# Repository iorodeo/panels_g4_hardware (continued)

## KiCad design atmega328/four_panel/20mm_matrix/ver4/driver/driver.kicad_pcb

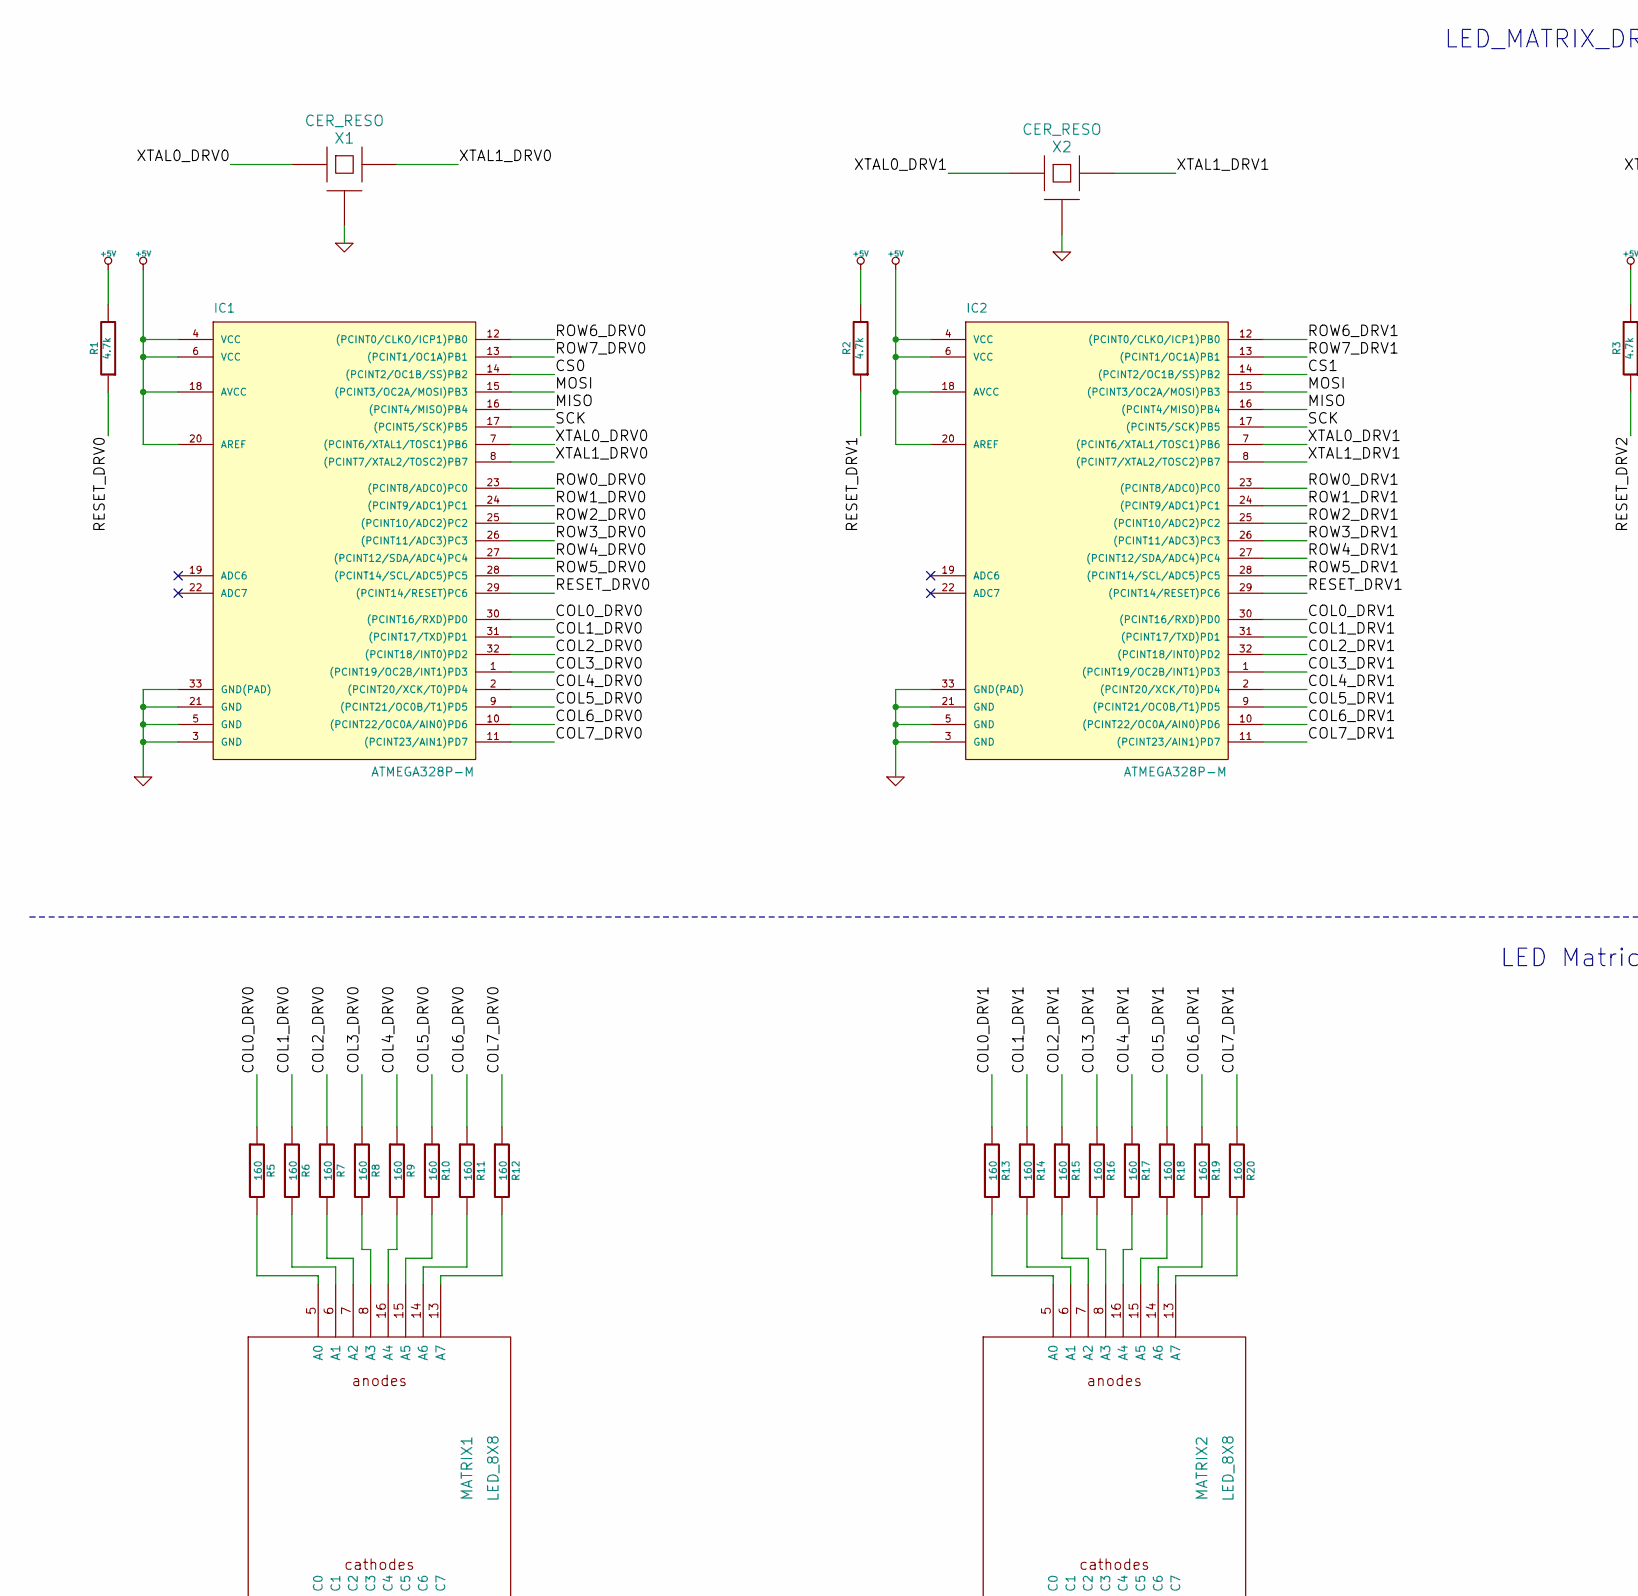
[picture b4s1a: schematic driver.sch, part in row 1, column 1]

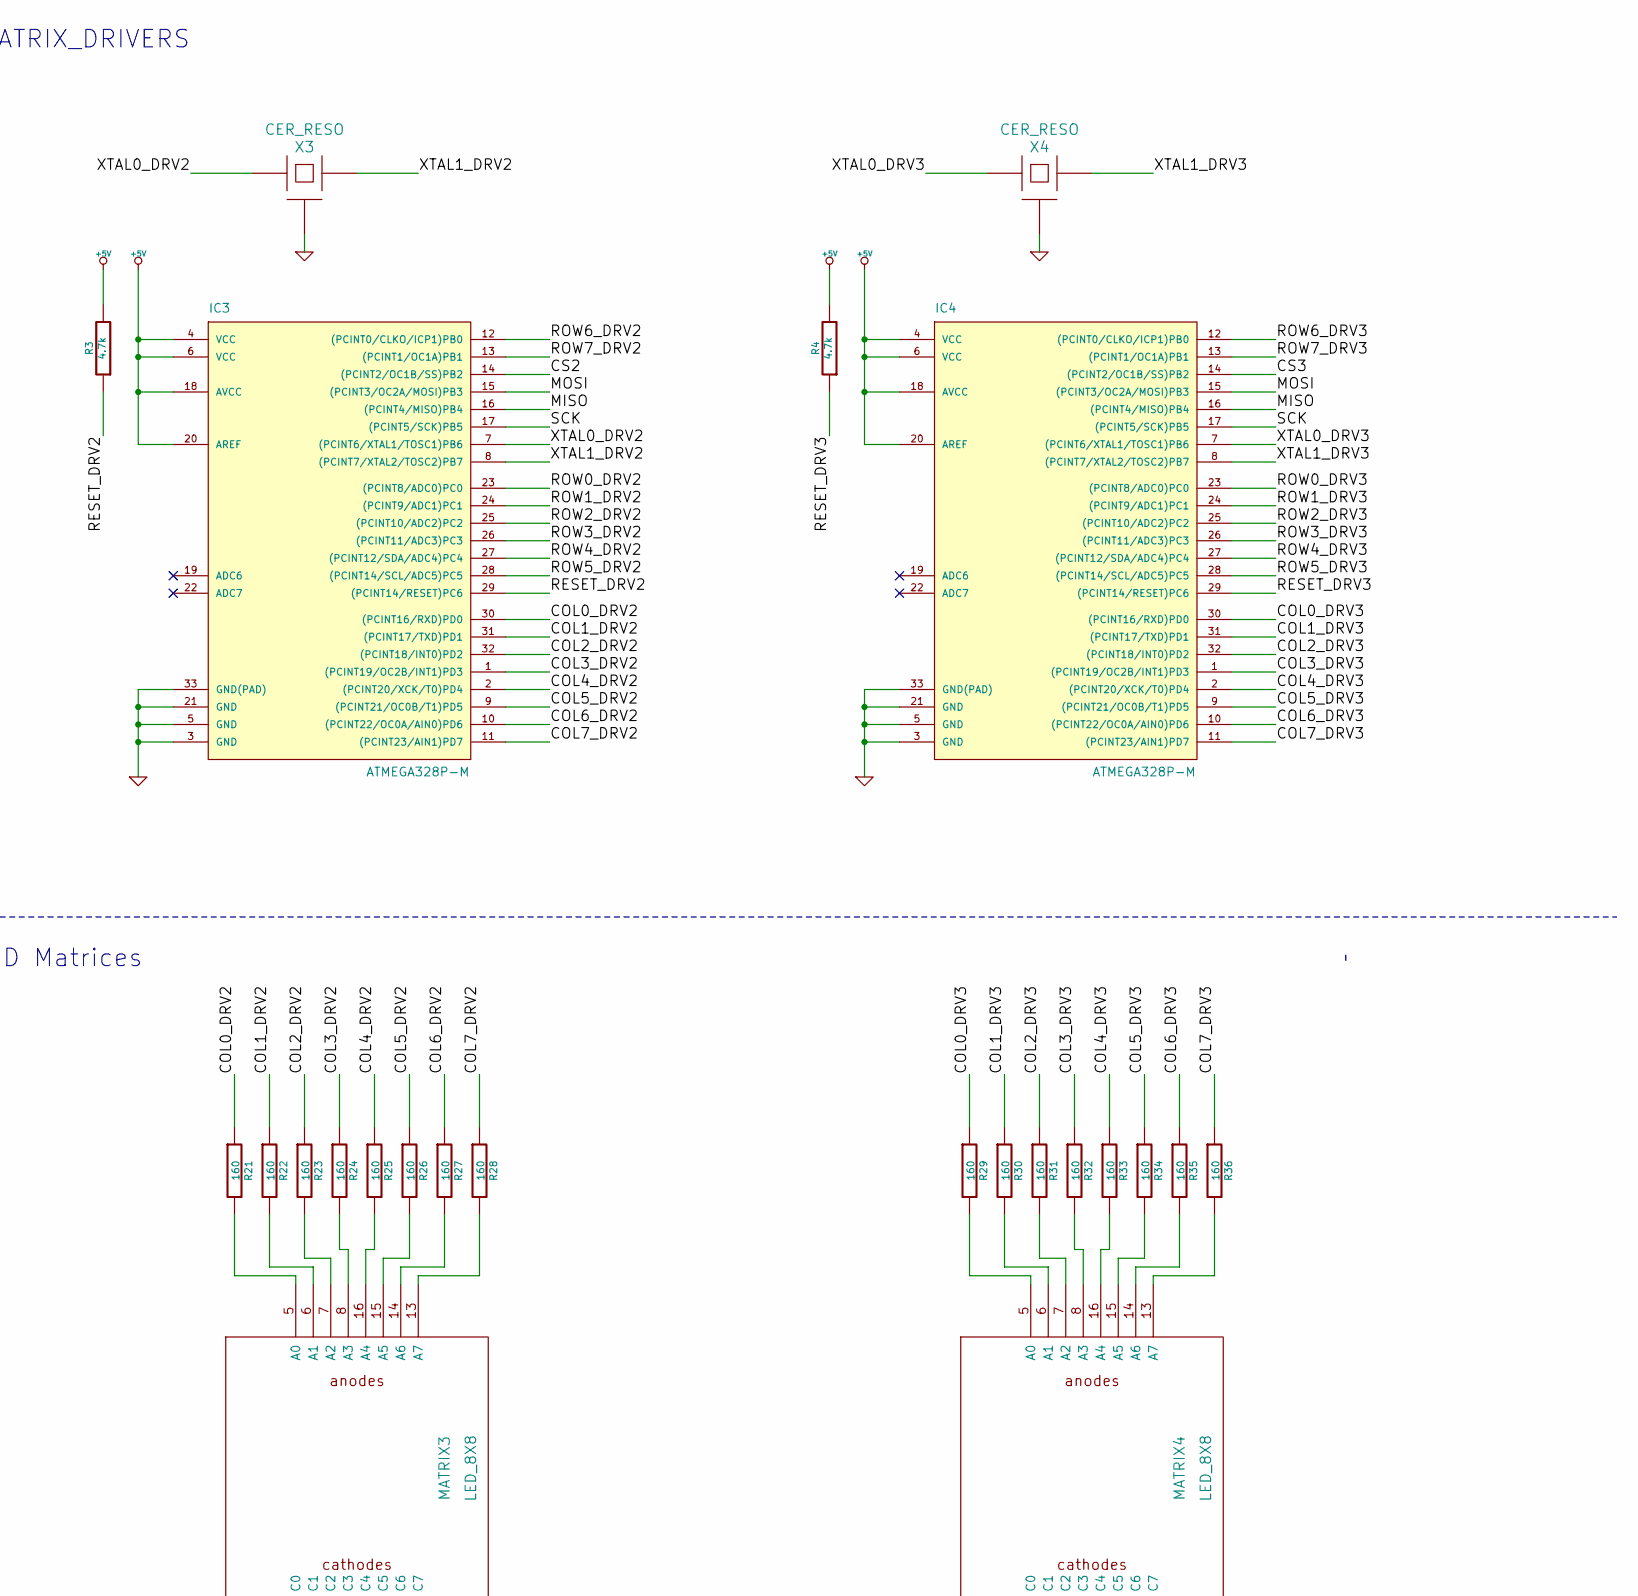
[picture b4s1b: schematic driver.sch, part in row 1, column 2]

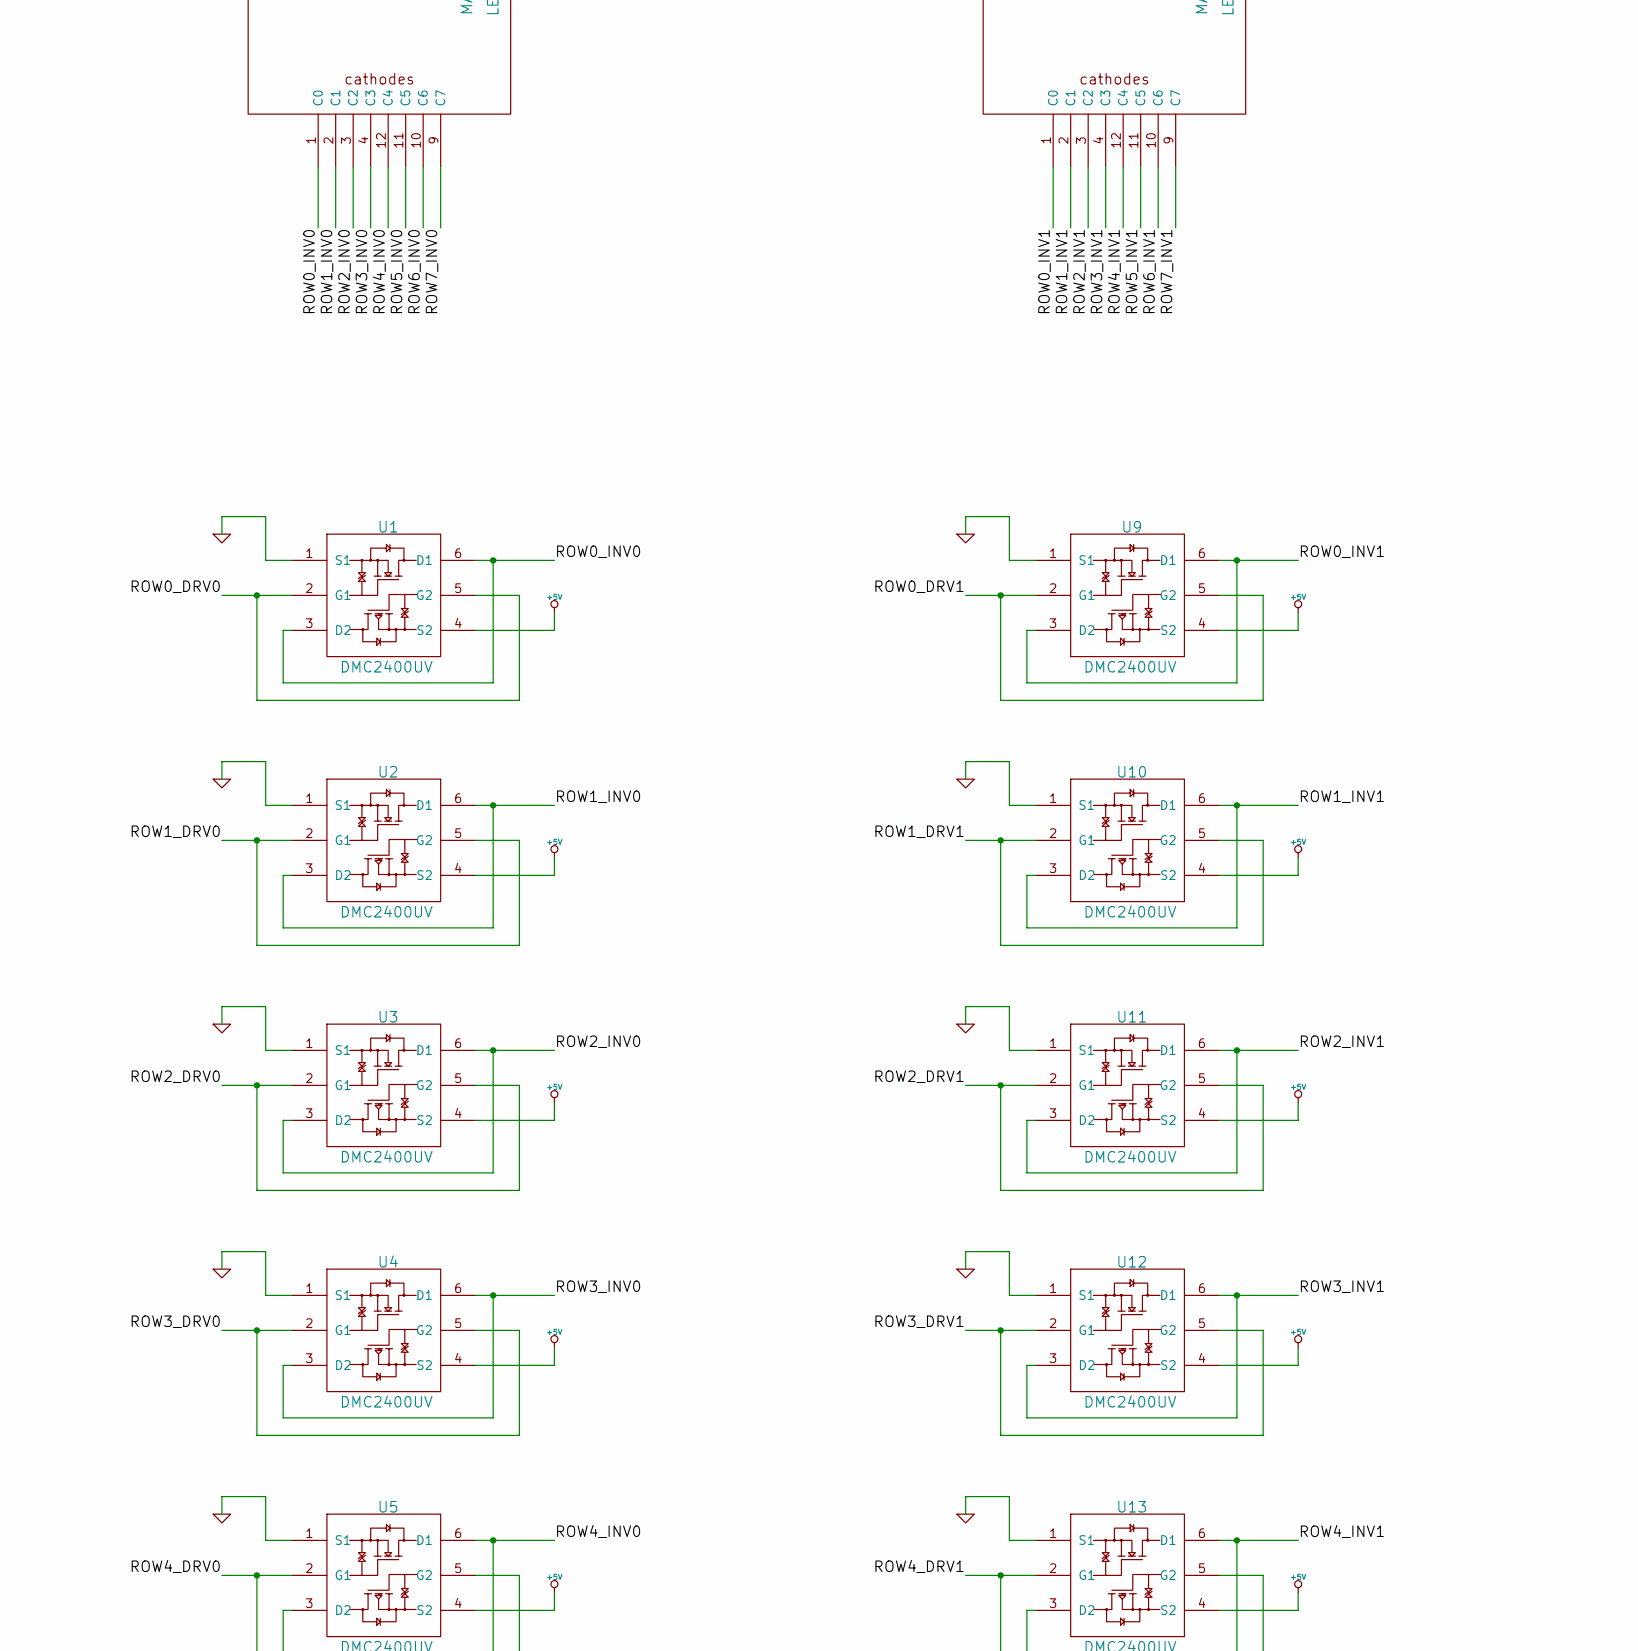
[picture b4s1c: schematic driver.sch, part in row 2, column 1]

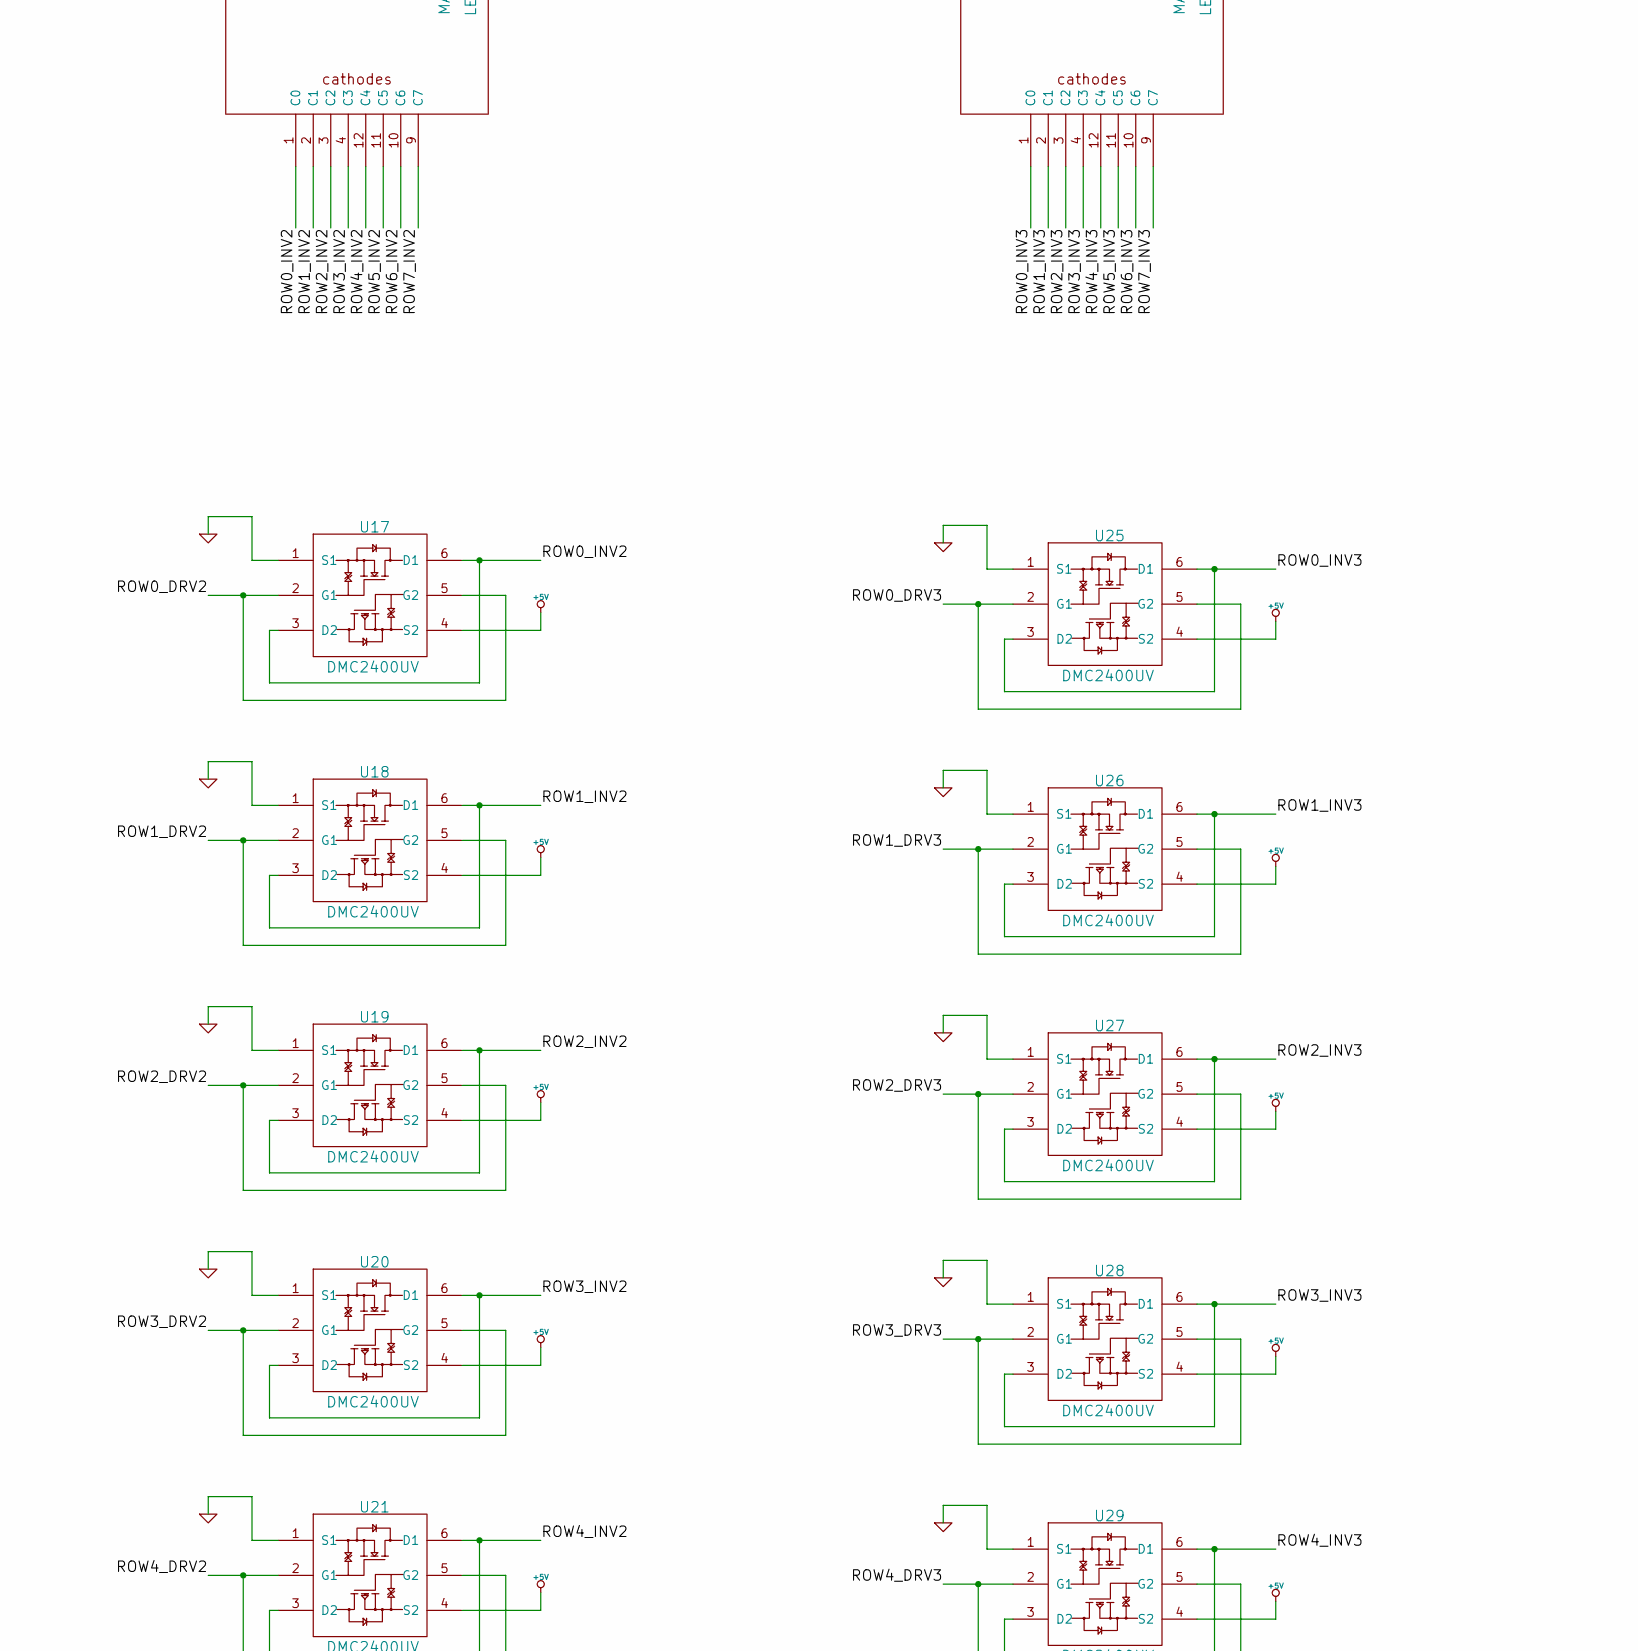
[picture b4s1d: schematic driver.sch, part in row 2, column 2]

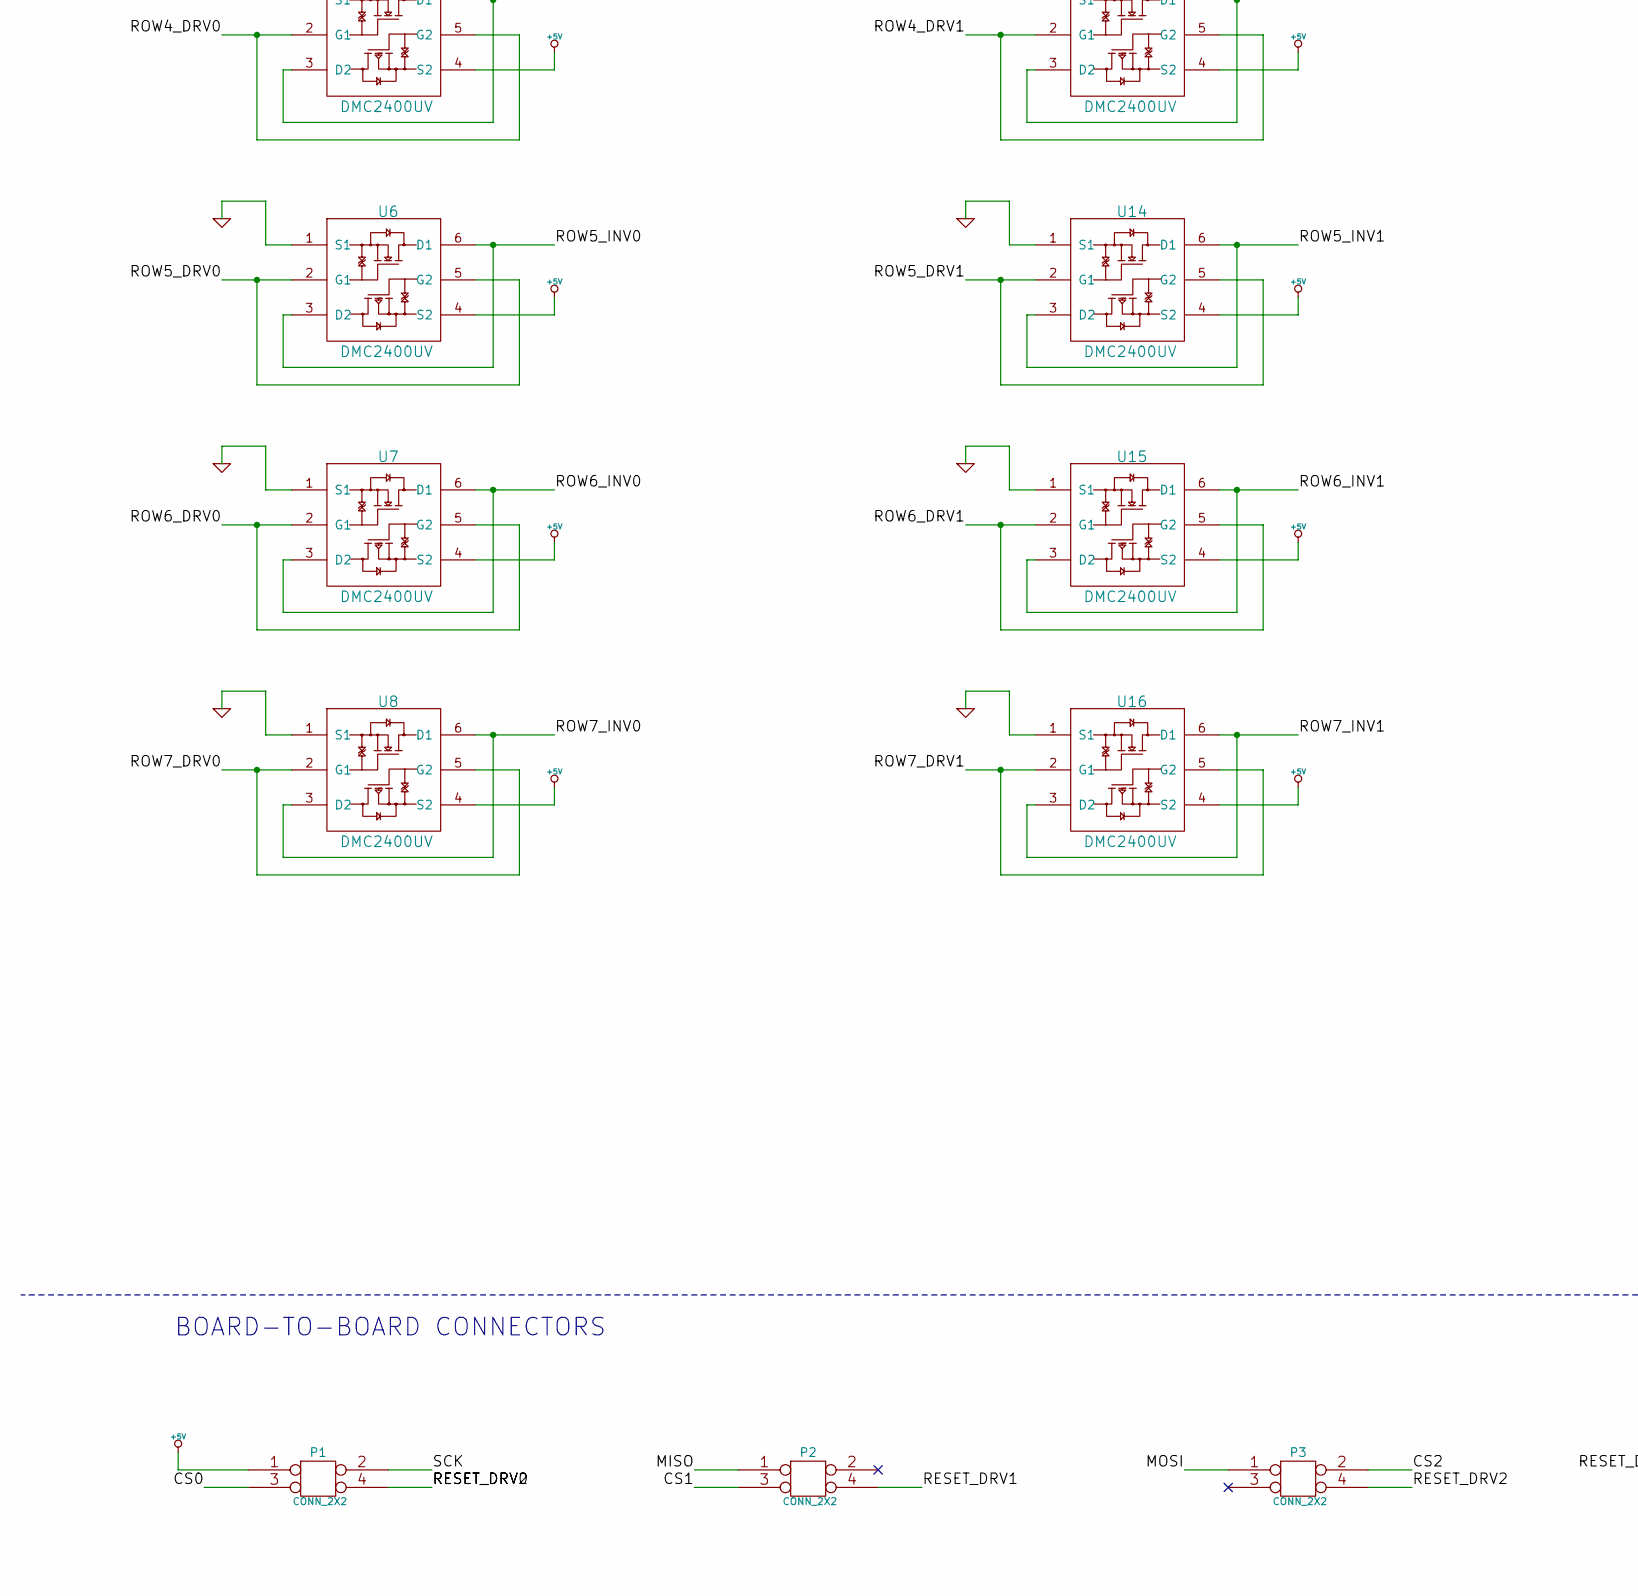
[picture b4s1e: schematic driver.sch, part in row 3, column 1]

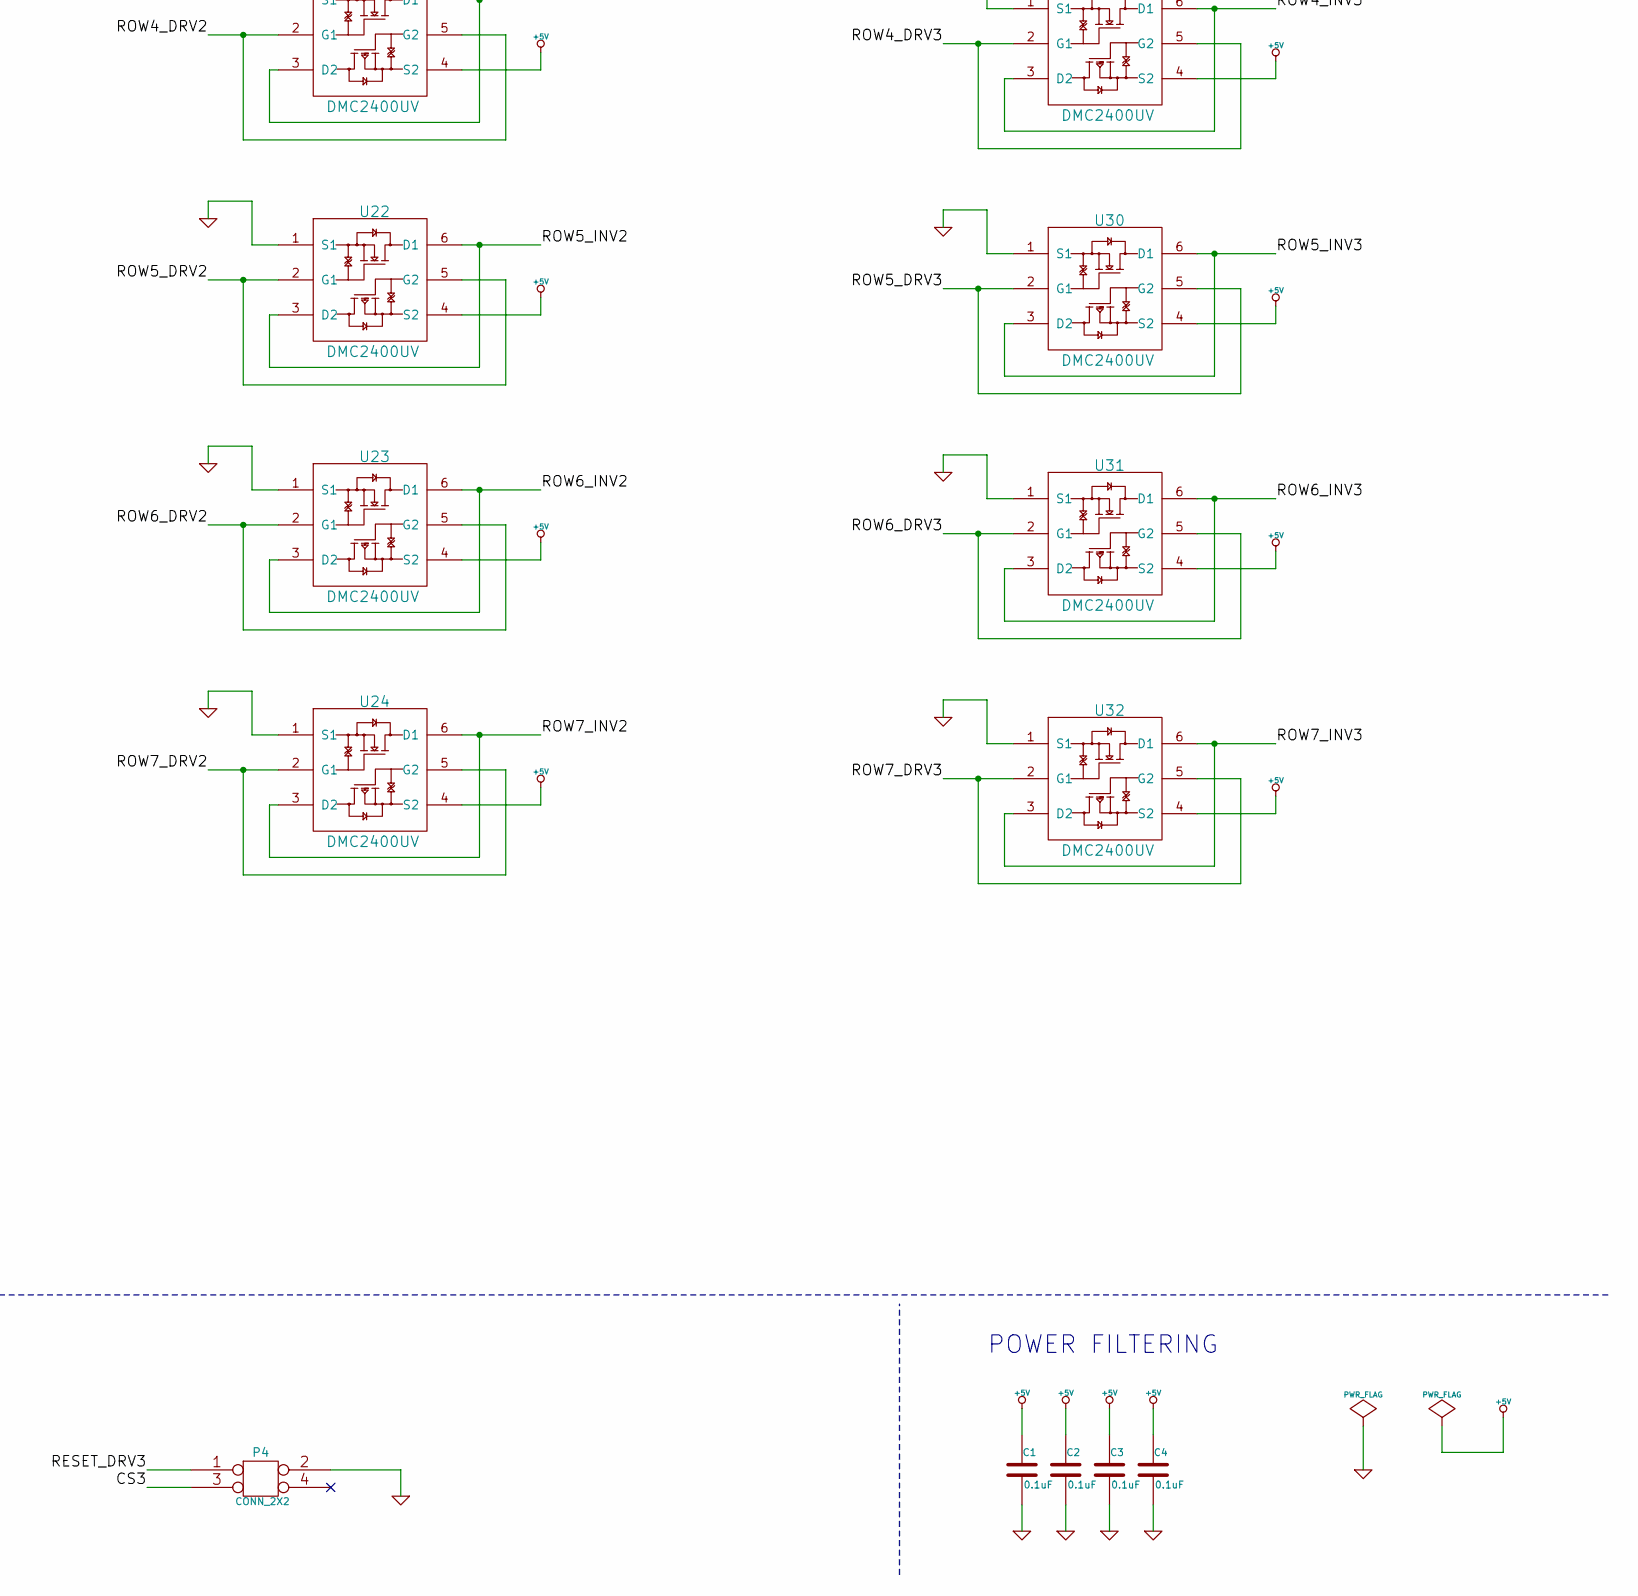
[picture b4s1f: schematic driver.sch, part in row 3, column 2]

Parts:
C1, C2, C3, C4: 0.1uF
IC1, IC2, IC3, IC4: ATMEGA328P-M; MLF/QFN32
MATRIX1, MATRIX2, MATRIX3, MATRIX4: LED_8X8
P1, P2, P3, P4: CONN_2X2
R1, R2, R3, R4: 4.7k
R5, R6, R7, R8, R9, R10, R11, R12, R13, R14, R15, R16, R17, R18, R19, R20, R21, R22, R23, R24, R25, R26, R27, R28, R29, R30, R31, R32, R33, R34, R35, R36: 160
U1, U2, U3, U4, U5, U6, U7, U8, U9, U10, U11, U12, U13, U14, U15, U16, U17, U18, U19, U20, U21, U22, U23, U24, U25, U26, U27, U28, U29, U30, U31, U32: DMC2400UV
X1, X2, X3, X4: CER_RESO

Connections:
+5V: C1.1, C2.1, C3.1, C4.1, IC1.4 (VCC), IC1.6 (VCC), IC1.18 (AVCC), IC1.20 (AREF), IC2.4 (VCC), IC2.6 (VCC), IC2.18 (AVCC), IC2.20 (AREF), IC3.4 (VCC), IC3.6 (VCC), IC3.18 (AVCC), IC3.20 (AREF), IC4.4 (VCC), IC4.6 (VCC), IC4.18 (AVCC), IC4.20 (AREF), P1.1, R1.2, R2.2, R3.2, R4.2, U1.4 (S2), U2.4 (S2), U3.4 (S2), U4.4 (S2), U5.4 (S2), U6.4 (S2), U7.4 (S2), U8.4 (S2), U9.4 (S2), U10.4 (S2), U11.4 (S2), U12.4 (S2), U13.4 (S2), U14.4 (S2), U15.4 (S2), U16.4 (S2), U17.4 (S2), U18.4 (S2), U19.4 (S2), U20.4 (S2), U21.4 (S2), U22.4 (S2), U23.4 (S2), U24.4 (S2), U25.4 (S2), U26.4 (S2), U27.4 (S2), U28.4 (S2), U29.4 (S2), U30.4 (S2), U31.4 (S2), U32.4 (S2)
/COL0_DRV0: IC1.30 ((PCINT16/RXD)PD0), R5.1
/COL0_DRV1: IC2.30 ((PCINT16/RXD)PD0), R13.1
/COL0_DRV2: IC3.30 ((PCINT16/RXD)PD0), R21.1
/COL0_DRV3: IC4.30 ((PCINT16/RXD)PD0), R29.1
/COL1_DRV0: IC1.31 ((PCINT17/TXD)PD1), R6.1
/COL1_DRV1: IC2.31 ((PCINT17/TXD)PD1), R14.1
/COL1_DRV2: IC3.31 ((PCINT17/TXD)PD1), R22.1
/COL1_DRV3: IC4.31 ((PCINT17/TXD)PD1), R30.1
/COL2_DRV0: IC1.32 ((PCINT18/INT0)PD2), R7.1
/COL2_DRV1: IC2.32 ((PCINT18/INT0)PD2), R15.1
/COL2_DRV2: IC3.32 ((PCINT18/INT0)PD2), R23.1
/COL2_DRV3: IC4.32 ((PCINT18/INT0)PD2), R31.1
/COL3_DRV0: IC1.1 ((PCINT19/OC2B/INT1)PD3), R8.1
/COL3_DRV1: IC2.1 ((PCINT19/OC2B/INT1)PD3), R16.1
/COL3_DRV2: IC3.1 ((PCINT19/OC2B/INT1)PD3), R24.1
/COL3_DRV3: IC4.1 ((PCINT19/OC2B/INT1)PD3), R32.1
/COL4_DRV0: IC1.2 ((PCINT20/XCK/T0)PD4), R9.1
/COL4_DRV1: IC2.2 ((PCINT20/XCK/T0)PD4), R17.1
/COL4_DRV2: IC3.2 ((PCINT20/XCK/T0)PD4), R25.1
/COL4_DRV3: IC4.2 ((PCINT20/XCK/T0)PD4), R33.1
/COL5_DRV0: IC1.9 ((PCINT21/OC0B/T1)PD5), R10.1
/COL5_DRV1: IC2.9 ((PCINT21/OC0B/T1)PD5), R18.1
/COL5_DRV2: IC3.9 ((PCINT21/OC0B/T1)PD5), R26.1
/COL5_DRV3: IC4.9 ((PCINT21/OC0B/T1)PD5), R34.1
/COL6_DRV0: IC1.10 ((PCINT22/OC0A/AIN0)PD6), R11.1
/COL6_DRV1: IC2.10 ((PCINT22/OC0A/AIN0)PD6), R19.1
/COL6_DRV2: IC3.10 ((PCINT22/OC0A/AIN0)PD6), R27.1
/COL6_DRV3: IC4.10 ((PCINT22/OC0A/AIN0)PD6), R35.1
/COL7_DRV0: IC1.11 ((PCINT23/AIN1)PD7), R12.1
/COL7_DRV1: IC2.11 ((PCINT23/AIN1)PD7), R20.1
/COL7_DRV2: IC3.11 ((PCINT23/AIN1)PD7), R28.1
/COL7_DRV3: IC4.11 ((PCINT23/AIN1)PD7), R36.1
/CS0: IC1.14 ((PCINT2/OC1B/SS)PB2), P1.3
/CS1: IC2.14 ((PCINT2/OC1B/SS)PB2), P2.3
/CS2: IC3.14 ((PCINT2/OC1B/SS)PB2), P3.2
/CS3: IC4.14 ((PCINT2/OC1B/SS)PB2), P4.3
/MISO: IC1.16 ((PCINT4/MISO)PB4), IC2.16 ((PCINT4/MISO)PB4), IC3.16 ((PCINT4/MISO)PB4), IC4.16 ((PCINT4/MISO)PB4), P2.1
/MOSI: IC1.15 ((PCINT3/OC2A/MOSI)PB3), IC2.15 ((PCINT3/OC2A/MOSI)PB3), IC3.15 ((PCINT3/OC2A/MOSI)PB3), IC4.15 ((PCINT3/OC2A/MOSI)PB3), P3.1
/RESET_DRV0: IC1.29 ((PCINT14/RESET)PC6), IC3.29 ((PCINT14/RESET)PC6), P1.4, P3.4, R1.1, R3.1
/RESET_DRV1: IC2.29 ((PCINT14/RESET)PC6), P2.4, R2.1
/RESET_DRV3: IC4.29 ((PCINT14/RESET)PC6), P4.1, R4.1
/ROW0_DRV0: IC1.23 ((PCINT8/ADC0)PC0), U1.2 (G1), U1.5 (G2)
/ROW0_DRV1: IC2.23 ((PCINT8/ADC0)PC0), U9.2 (G1), U9.5 (G2)
/ROW0_DRV2: IC3.23 ((PCINT8/ADC0)PC0), U17.2 (G1), U17.5 (G2)
/ROW0_DRV3: IC4.23 ((PCINT8/ADC0)PC0), U25.2 (G1), U25.5 (G2)
/ROW0_INV0: MATRIX1.1 (C0), U1.3 (D2), U1.6 (D1)
/ROW0_INV1: MATRIX2.1 (C0), U9.3 (D2), U9.6 (D1)
/ROW0_INV2: MATRIX3.1 (C0), U17.3 (D2), U17.6 (D1)
/ROW0_INV3: MATRIX4.1 (C0), U25.3 (D2), U25.6 (D1)
/ROW1_DRV0: IC1.24 ((PCINT9/ADC1)PC1), U2.2 (G1), U2.5 (G2)
/ROW1_DRV1: IC2.24 ((PCINT9/ADC1)PC1), U10.2 (G1), U10.5 (G2)
/ROW1_DRV2: IC3.24 ((PCINT9/ADC1)PC1), U18.2 (G1), U18.5 (G2)
/ROW1_DRV3: IC4.24 ((PCINT9/ADC1)PC1), U26.2 (G1), U26.5 (G2)
/ROW1_INV0: MATRIX1.2 (C1), U2.3 (D2), U2.6 (D1)
/ROW1_INV1: MATRIX2.2 (C1), U10.3 (D2), U10.6 (D1)
/ROW1_INV2: MATRIX3.2 (C1), U18.3 (D2), U18.6 (D1)
/ROW1_INV3: MATRIX4.2 (C1), U26.3 (D2), U26.6 (D1)
/ROW2_DRV0: IC1.25 ((PCINT10/ADC2)PC2), U3.2 (G1), U3.5 (G2)
/ROW2_DRV1: IC2.25 ((PCINT10/ADC2)PC2), U11.2 (G1), U11.5 (G2)
/ROW2_DRV2: IC3.25 ((PCINT10/ADC2)PC2), U19.2 (G1), U19.5 (G2)
/ROW2_DRV3: IC4.25 ((PCINT10/ADC2)PC2), U27.2 (G1), U27.5 (G2)
/ROW2_INV0: MATRIX1.3 (C2), U3.3 (D2), U3.6 (D1)
/ROW2_INV1: MATRIX2.3 (C2), U11.3 (D2), U11.6 (D1)
/ROW2_INV2: MATRIX3.3 (C2), U19.3 (D2), U19.6 (D1)
/ROW2_INV3: MATRIX4.3 (C2), U27.3 (D2), U27.6 (D1)
/ROW3_DRV0: IC1.26 ((PCINT11/ADC3)PC3), U4.2 (G1), U4.5 (G2)
/ROW3_DRV1: IC2.26 ((PCINT11/ADC3)PC3), U12.2 (G1), U12.5 (G2)
/ROW3_DRV2: IC3.26 ((PCINT11/ADC3)PC3), U20.2 (G1), U20.5 (G2)
/ROW3_DRV3: IC4.26 ((PCINT11/ADC3)PC3), U28.2 (G1), U28.5 (G2)
/ROW3_INV0: MATRIX1.4 (C3), U4.3 (D2), U4.6 (D1)
/ROW3_INV1: MATRIX2.4 (C3), U12.3 (D2), U12.6 (D1)
/ROW3_INV2: MATRIX3.4 (C3), U20.3 (D2), U20.6 (D1)
/ROW3_INV3: MATRIX4.4 (C3), U28.3 (D2), U28.6 (D1)
/ROW4_DRV0: IC1.27 ((PCINT12/SDA/ADC4)PC4), U5.2 (G1), U5.5 (G2)
/ROW4_DRV1: IC2.27 ((PCINT12/SDA/ADC4)PC4), U13.2 (G1), U13.5 (G2)
/ROW4_DRV2: IC3.27 ((PCINT12/SDA/ADC4)PC4), U21.2 (G1), U21.5 (G2)
/ROW4_DRV3: IC4.27 ((PCINT12/SDA/ADC4)PC4), U29.2 (G1), U29.5 (G2)
/ROW4_INV0: MATRIX1.12 (C4), U5.3 (D2), U5.6 (D1)
/ROW4_INV1: MATRIX2.12 (C4), U13.3 (D2), U13.6 (D1)
/ROW4_INV2: MATRIX3.12 (C4), U21.3 (D2), U21.6 (D1)
/ROW4_INV3: MATRIX4.12 (C4), U29.3 (D2), U29.6 (D1)
/ROW5_DRV0: IC1.28 ((PCINT14/SCL/ADC5)PC5), U6.2 (G1), U6.5 (G2)
/ROW5_DRV1: IC2.28 ((PCINT14/SCL/ADC5)PC5), U14.2 (G1), U14.5 (G2)
/ROW5_DRV2: IC3.28 ((PCINT14/SCL/ADC5)PC5), U22.2 (G1), U22.5 (G2)
/ROW5_DRV3: IC4.28 ((PCINT14/SCL/ADC5)PC5), U30.2 (G1), U30.5 (G2)
/ROW5_INV0: MATRIX1.11 (C5), U6.3 (D2), U6.6 (D1)
/ROW5_INV1: MATRIX2.11 (C5), U14.3 (D2), U14.6 (D1)
/ROW5_INV2: MATRIX3.11 (C5), U22.3 (D2), U22.6 (D1)
/ROW5_INV3: MATRIX4.11 (C5), U30.3 (D2), U30.6 (D1)
/ROW6_DRV0: IC1.12 ((PCINT0/CLKO/ICP1)PB0), U7.2 (G1), U7.5 (G2)
/ROW6_DRV1: IC2.12 ((PCINT0/CLKO/ICP1)PB0), U15.2 (G1), U15.5 (G2)
/ROW6_DRV2: IC3.12 ((PCINT0/CLKO/ICP1)PB0), U23.2 (G1), U23.5 (G2)
/ROW6_DRV3: IC4.12 ((PCINT0/CLKO/ICP1)PB0), U31.2 (G1), U31.5 (G2)
/ROW6_INV0: MATRIX1.10 (C6), U7.3 (D2), U7.6 (D1)
/ROW6_INV1: MATRIX2.10 (C6), U15.3 (D2), U15.6 (D1)
/ROW6_INV2: MATRIX3.10 (C6), U23.3 (D2), U23.6 (D1)
/ROW6_INV3: MATRIX4.10 (C6), U31.3 (D2), U31.6 (D1)
/ROW7_DRV0: IC1.13 ((PCINT1/OC1A)PB1), U8.2 (G1), U8.5 (G2)
/ROW7_DRV1: IC2.13 ((PCINT1/OC1A)PB1), U16.2 (G1), U16.5 (G2)
/ROW7_DRV2: IC3.13 ((PCINT1/OC1A)PB1), U24.2 (G1), U24.5 (G2)
/ROW7_DRV3: IC4.13 ((PCINT1/OC1A)PB1), U32.2 (G1), U32.5 (G2)
/ROW7_INV0: MATRIX1.9 (C7), U8.3 (D2), U8.6 (D1)
/ROW7_INV1: MATRIX2.9 (C7), U16.3 (D2), U16.6 (D1)
/ROW7_INV2: MATRIX3.9 (C7), U24.3 (D2), U24.6 (D1)
/ROW7_INV3: MATRIX4.9 (C7), U32.3 (D2), U32.6 (D1)
/SCK: IC1.17 ((PCINT5/SCK)PB5), IC2.17 ((PCINT5/SCK)PB5), IC3.17 ((PCINT5/SCK)PB5), IC4.17 ((PCINT5/SCK)PB5), P1.2
/XTAL0_DRV0: IC1.7 ((PCINT6/XTAL1/TOSC1)PB6), X1.1
/XTAL0_DRV1: IC2.7 ((PCINT6/XTAL1/TOSC1)PB6), X2.1
/XTAL0_DRV2: IC3.7 ((PCINT6/XTAL1/TOSC1)PB6), X3.1
/XTAL0_DRV3: IC4.7 ((PCINT6/XTAL1/TOSC1)PB6), X4.1
/XTAL1_DRV0: IC1.8 ((PCINT7/XTAL2/TOSC2)PB7), X1.3
/XTAL1_DRV1: IC2.8 ((PCINT7/XTAL2/TOSC2)PB7), X2.3
/XTAL1_DRV2: IC3.8 ((PCINT7/XTAL2/TOSC2)PB7), X3.3
/XTAL1_DRV3: IC4.8 ((PCINT7/XTAL2/TOSC2)PB7), X4.3
GND: C1.2, C2.2, C3.2, C4.2, IC1.3 (GND), IC1.5 (GND), IC1.21 (GND), IC1.33 (GND(PAD)), IC2.3 (GND), IC2.5 (GND), IC2.21 (GND), IC2.33 (GND(PAD)), IC3.3 (GND), IC3.5 (GND), IC3.21 (GND), IC3.33 (GND(PAD)), IC4.3 (GND), IC4.5 (GND), IC4.21 (GND), IC4.33 (GND(PAD)), P4.2, U1.1 (S1), U2.1 (S1), U3.1 (S1), U4.1 (S1), U5.1 (S1), U6.1 (S1), U7.1 (S1), U8.1 (S1), U9.1 (S1), U10.1 (S1), U11.1 (S1), U12.1 (S1), U13.1 (S1), U14.1 (S1), U15.1 (S1), U16.1 (S1), U17.1 (S1), U18.1 (S1), U19.1 (S1), U20.1 (S1), U21.1 (S1), U22.1 (S1), U23.1 (S1), U24.1 (S1), U25.1 (S1), U26.1 (S1), U27.1 (S1), U28.1 (S1), U29.1 (S1), U30.1 (S1), U31.1 (S1), U32.1 (S1), X1.2 (GND), X2.2 (GND), X3.2 (GND), X4.2 (GND)
unnamed: MATRIX1.8 (A3), R8.2
unnamed: MATRIX1.7 (A2), R7.2
unnamed: MATRIX1.6 (A1), R6.2
unnamed: MATRIX1.5 (A0), R5.2
unnamed: MATRIX3.6 (A1), R22.2
unnamed: MATRIX3.5 (A0), R21.2
unnamed: MATRIX3.7 (A2), R23.2
unnamed: MATRIX3.8 (A3), R24.2
unnamed: MATRIX2.8 (A3), R16.2
unnamed: MATRIX2.7 (A2), R15.2
unnamed: MATRIX2.6 (A1), R14.2
unnamed: MATRIX2.5 (A0), R13.2
unnamed: MATRIX3.15 (A5), R26.2
unnamed: MATRIX4.8 (A3), R32.2
unnamed: MATRIX4.7 (A2), R31.2
unnamed: MATRIX4.6 (A1), R30.2
unnamed: MATRIX4.5 (A0), R29.2
unnamed: MATRIX3.13 (A7), R28.2
unnamed: MATRIX3.14 (A6), R27.2
unnamed: MATRIX3.16 (A4), R25.2
unnamed: MATRIX4.14 (A6), R35.2
unnamed: MATRIX4.15 (A5), R34.2
unnamed: MATRIX4.16 (A4), R33.2
unnamed: MATRIX4.13 (A7), R36.2
unnamed: MATRIX2.15 (A5), R18.2
unnamed: MATRIX2.13 (A7), R20.2
unnamed: MATRIX2.14 (A6), R19.2
unnamed: MATRIX2.16 (A4), R17.2
unnamed: MATRIX1.16 (A4), R9.2
unnamed: MATRIX1.13 (A7), R12.2
unnamed: MATRIX1.14 (A6), R11.2
unnamed: MATRIX1.15 (A5), R10.2

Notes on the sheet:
LED_MATRIX_DRIVERS
POWER FILTERING
BOARD-TO-BOARD CONNECTORS
LED Matrices

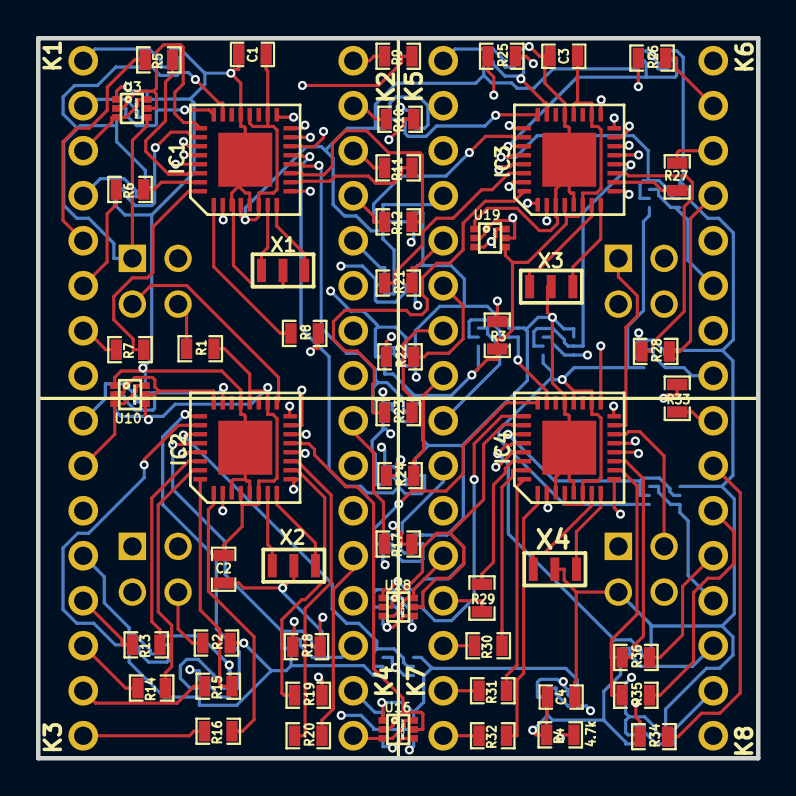
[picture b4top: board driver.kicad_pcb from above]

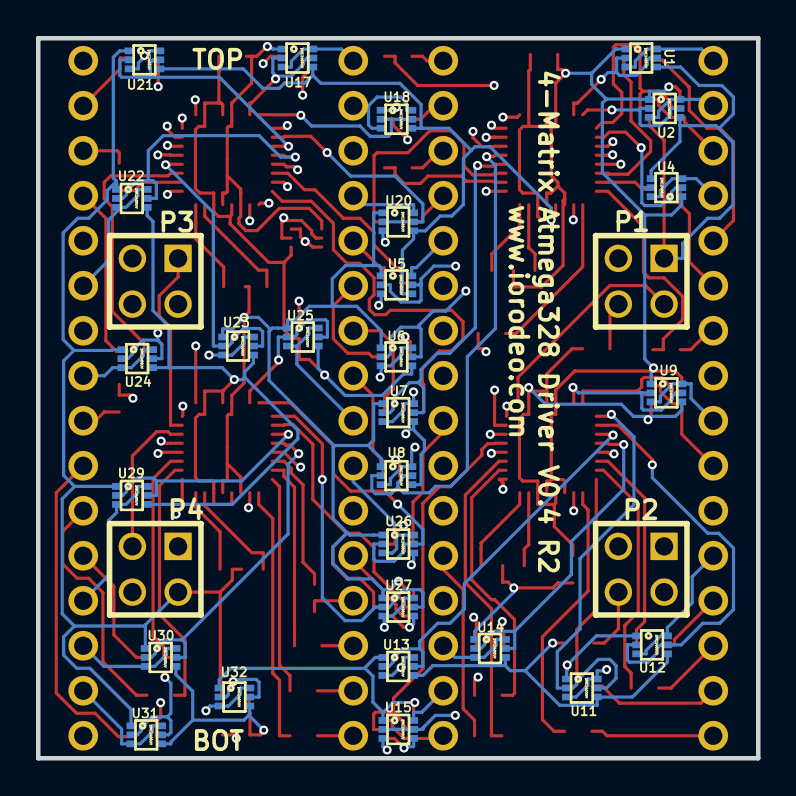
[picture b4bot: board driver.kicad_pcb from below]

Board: 4 copper layers, 40.0 x 40.0 mm, 88 parts (31 on the bottom side), 148 nets.
